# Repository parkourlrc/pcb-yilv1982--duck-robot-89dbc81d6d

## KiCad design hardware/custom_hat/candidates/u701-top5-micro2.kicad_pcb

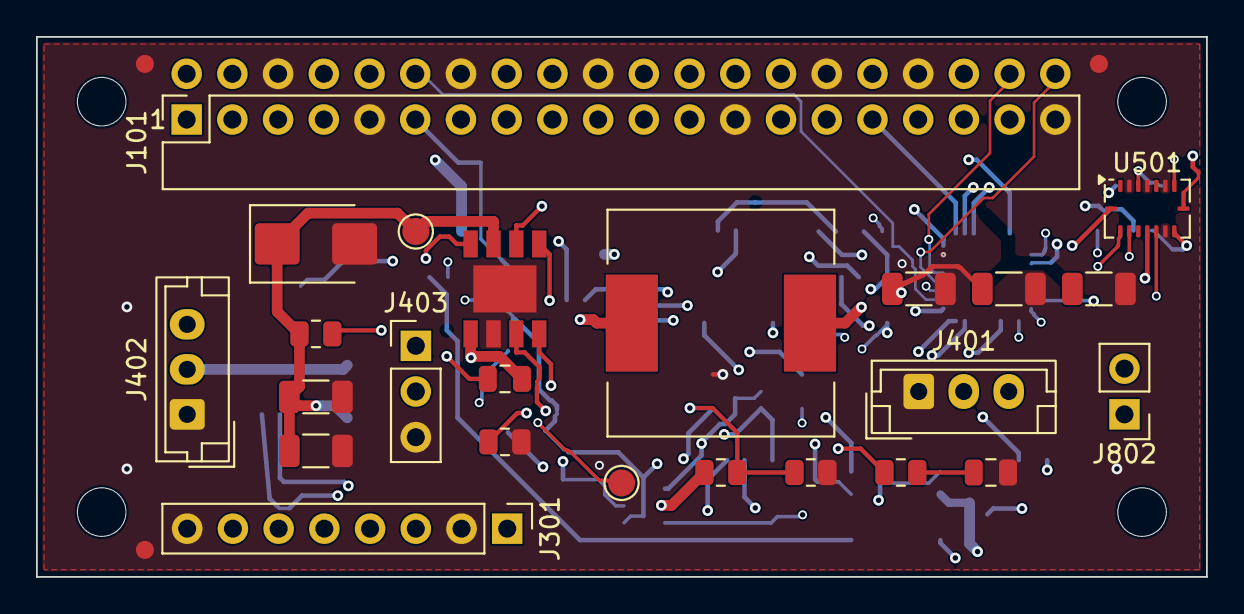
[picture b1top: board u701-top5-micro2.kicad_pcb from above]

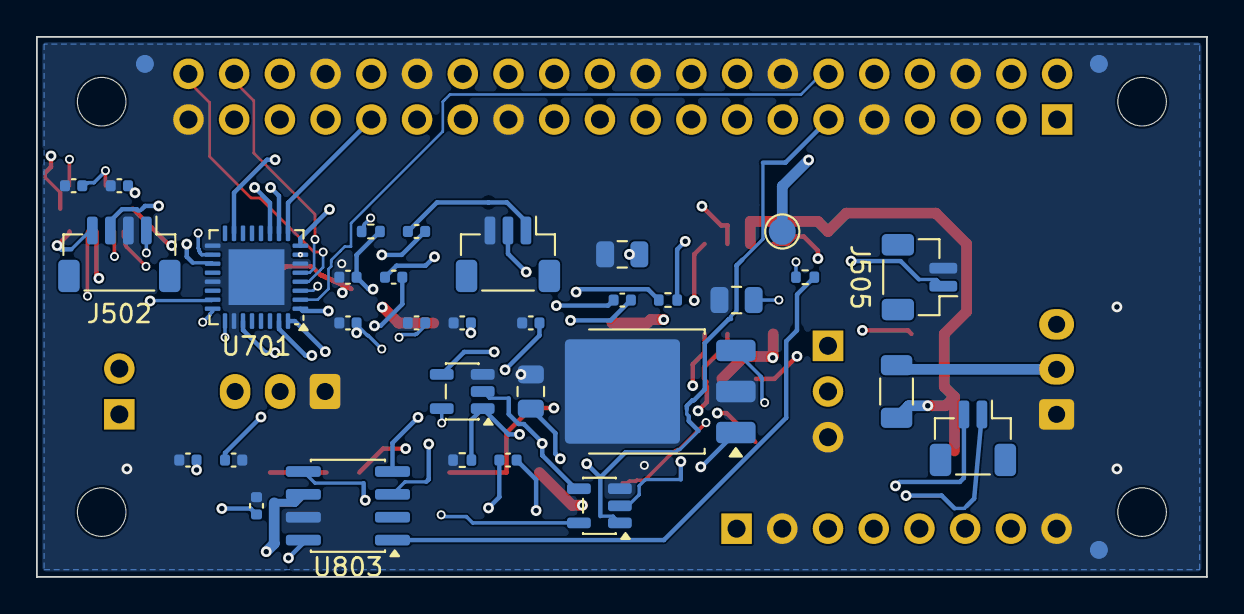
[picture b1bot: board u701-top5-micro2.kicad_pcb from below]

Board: 4 copper layers, 65.0 x 30.0 mm, 66 parts (35 on the bottom side), 41 nets.

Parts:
C301: 3.3nF; C_0805_2012Metric
C302: 100nF; C_0805_2012Metric
C303, C304: 10uF; C_1206_3216Metric
C305, C306: 22uF; C_1206_3216Metric
C307: 22uF reserve; C_1206_3216Metric
C308, C309: 1uF; C_0805_2012Metric
C310, C312, C319, C320, C327: 100nF; C_0402_1005Metric
C311, C313, C315, C321, C322, C325, C326: 1uF; C_0402_1005Metric
C317, C318: 10uF; C_0402_1005Metric
C323: 10uF; C_0805_2012Metric
D301: SMBJ12A (fitted); D_SMB
FID1, FID2, FID3, FID4, FID5, FID6: Fiducial_1mm
H1, H2, H3, H4: MountingHole_2.7mm_M2.5
J101: RADXA_ZERO_3W_40P; PinSocket_2x20_P2.54mm_Vertical
J301: POWER_AND_RAILS; PinHeader_1x08_P2.54mm_Vertical
J401: DYNAMIXEL_TTL_1; JST_EH_B3B-EH-A_1x03_P2.50mm_Vertical
J402: DYNAMIXEL_TTL_2; JST_EH_B3B-EH-A_1x03_P2.50mm_Vertical
J403: HOST_UART2; PinHeader_1x03_P2.54mm_Vertical
J502: TOF_I2C5; JST_SH_BM04B-SRSS-TB_1x04-1MP_P1.00mm_Vertical
J504: AUDIO_OUT_SH; JST_SH_BM03B-SRSS-TB_1x03-1MP_P1.00mm_Vertical
J505: MIC_IN; JST_SH_BM02B-SRSS-TB_1x02-1MP_P1.00mm_Vertical
J506: SPEAKER; JST_SH_BM02B-SRSS-TB_1x02-1MP_P1.00mm_Vertical
J802: IMU_INT_TP; PinHeader_1x02_P2.54mm_Vertical
L301: 5.5uH; L_12x12mm_H8mm
R301: 52.3k; R_0805_2012Metric
R302: 10k; R_0805_2012Metric
R303: 200k; R_0805_2012Metric
R304: 14k; R_0805_2012Metric
R305: 100k; R_0805_2012Metric
R308: 10k; R_0402_1005Metric
R309: 0R; R_1206_3216Metric
R310, R311: 100k; R_0402_1005Metric
R312: 2.2k; R_0402_1005Metric
TP801: VBATT_2S_IN; TestPoint_Pad_D1.5mm
TP802: +5V; TestPoint_Pad_D1.5mm
TP803: +3V3; TestPoint_Pad_D1.5mm
U301: AP64350; SO-8EP_AP64350
U501: BMI088; Bosch_LGA-16_4.5x3mm_P0.5mm_LayoutBorder7x1y_ClockwisePinNu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
U701: TLV320AIC3104; VQFN-32-1EP_5x5mm_P0.5mm_EP3.1x3.1mm
U702: LP38693DT-1.8 codec 1V8; TO-252-3_TabPin2
U801: SN74LVC1G126; SOT-23-5
U802: SN74LVC1G125; SOT-23-5
U803: PAM8302A; SOIC-8_3.9x4.9mm_P1.27mm

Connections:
+1V8_CODEC: C309.1, C311.1, J301.6, U701.32, U702.1
+3V3: C308.1, C312.1, C313.1, C315.1, C319.1, C320.1, J101.1, J101.17, J301.4, J502.1, R308.2, R311.2, TP803.1, U501.3, U501.7, U501.11, U501.14, U501.15, U701.7, U701.18, U701.24, U701.25, U702.3, U801.5, U802.5
+5V: C305.1, C306.1, C307.1, C323.1, J101.2, J101.4, J301.3, L301.2, R301.1, TP802.1, U803.6
+5V_FB: R301.2, R302.1, U301.5
AUDIO_AMP_EN: R311.1, U803.1
AUDIO_AMP_INN: C322.1, U803.4
AUDIO_AMP_INP: C321.2, U803.3
AUDIO_HP_L: C317.1, U701.19
AUDIO_HP_R: C318.1, U701.23
AUDIO_L: C317.2, J504.1
AUDIO_LINE_L: C321.1, U701.27
AUDIO_MIC: C325.1, J505.1, R312.2
AUDIO_MIC_AC: C325.2, U701.10
AUDIO_MIC_BIAS: C327.1, R312.1, U701.15
AUDIO_MIC_REF: C326.2, U701.11
AUDIO_R: C318.2, J504.2
BMI_INT1_TP: J802.1, U501.16
BMI_INT3_TP: J802.2, U501.12
BUCK_BST: C302.1, U301.1
BUCK_COMP: R304.1, U301.6
BUCK_EN: R305.2, U301.3
BUCK_RT: R303.1, U301.4
BUCK_SW: C302.2, L301.1, U301.8
CODEC_RST: C310.1, R308.1, U701.31
COMP_RC: C301.1, R304.2
DXL_DATA: J401.3, J402.3, U801.4, U802.2
DXL_DIR: J101.11, R310.1, U801.1, U802.1
I2C5_SCL: J101.29, J502.3, U501.8, U701.8
I2C5_SDA: J101.31, J502.4, U501.9, U701.9
I2S_BCLK: J101.12, U701.2
I2S_LRCK: J101.35, U701.3
I2S_MCLK: J101.13, U701.1
I2S_SDI: J101.38, U701.5
I2S_SDO: J101.40, U701.4
POWER_GND: C301.2, C303.2, C304.2, C305.2, C306.2, C307.2, C308.2, C309.2, C310.2, C311.2, C312.2, C313.2, C315.2, C319.2, C320.2, C322.2, C323.2, C326.1, C327.2, D301.2, J101.6, J101.9, J101.14, J101.20, J101.25, J101.30, J101.34, J101.39, J301.2, J301.8, J401.1, J402.1, J403.3, J502.2, J504.3, J505.2, R302.2, R303.2, R310.2, U301.7, U301.9, U501.2, U501.4, U501.6, U501.10, U701.6, U701.17, U701.21, U701.26, U701.33, U702.2, U801.3, U802.3, U803.7
SERVO_VBAT: J301.7, J401.2, J402.2, R309.2
SPK_N: J506.2, U803.8
SPK_P: J506.1, U803.5
UART2_RX: J101.10, J403.2, U802.4
UART2_TX: J101.8, J403.1, U801.2
VBATT_2S_IN: C303.1, C304.1, D301.1, J301.1, R305.1, R309.1, TP801.1, U301.2

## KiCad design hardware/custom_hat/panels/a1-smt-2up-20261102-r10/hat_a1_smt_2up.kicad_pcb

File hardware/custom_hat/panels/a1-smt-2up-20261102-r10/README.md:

# 失败候选r10：勿用于制造

> **2026-11-03撤出现行，仅历史。** 此拼板缺第二单元Power类别映射；旧DRC0不代表规则完整。使用[r18](../a1-smt-2up-20261102-r18/README.md)并见[勘误](../../../../docs/references/扩展板邮票孔与电源修复/research.md)，本目录及派生文件不再用于制造。

源96dcce92…，但第二单元J301标签复制保存角270°，与原实际绘制角90°不一致，引入0.1101mm丝印间距。已修复生成器并由[r11](../a1-smt-2up-20261102-r11/README.md)替代。保留原文件与失败DRC供追溯，未外发/下单。

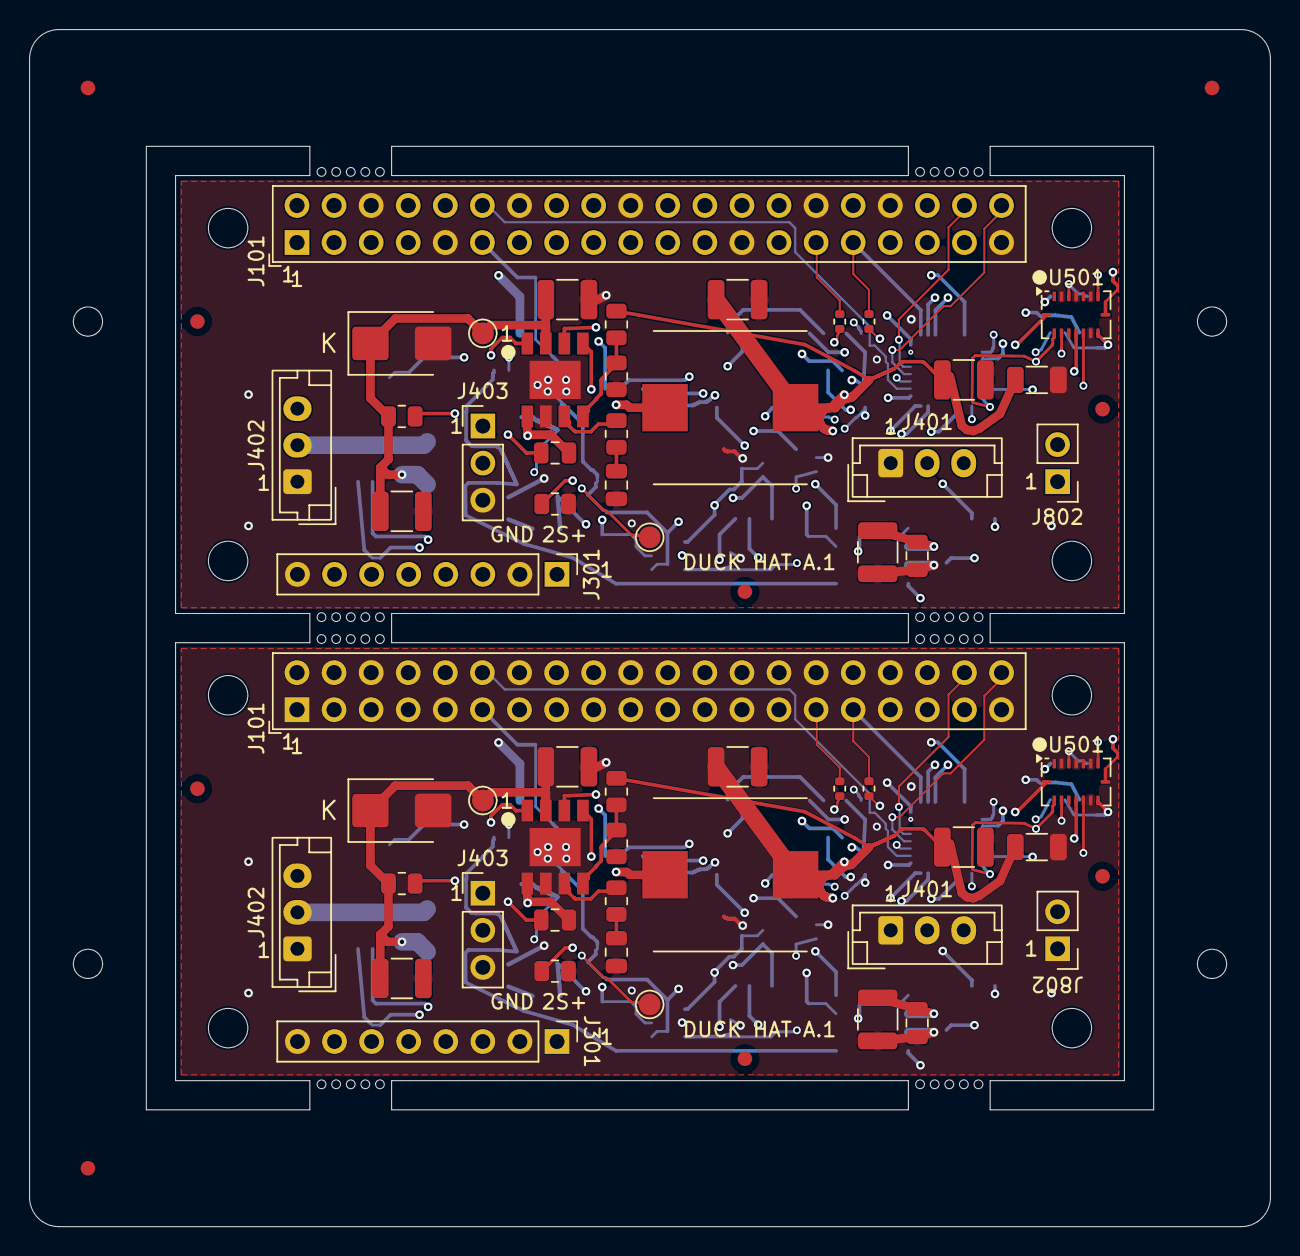
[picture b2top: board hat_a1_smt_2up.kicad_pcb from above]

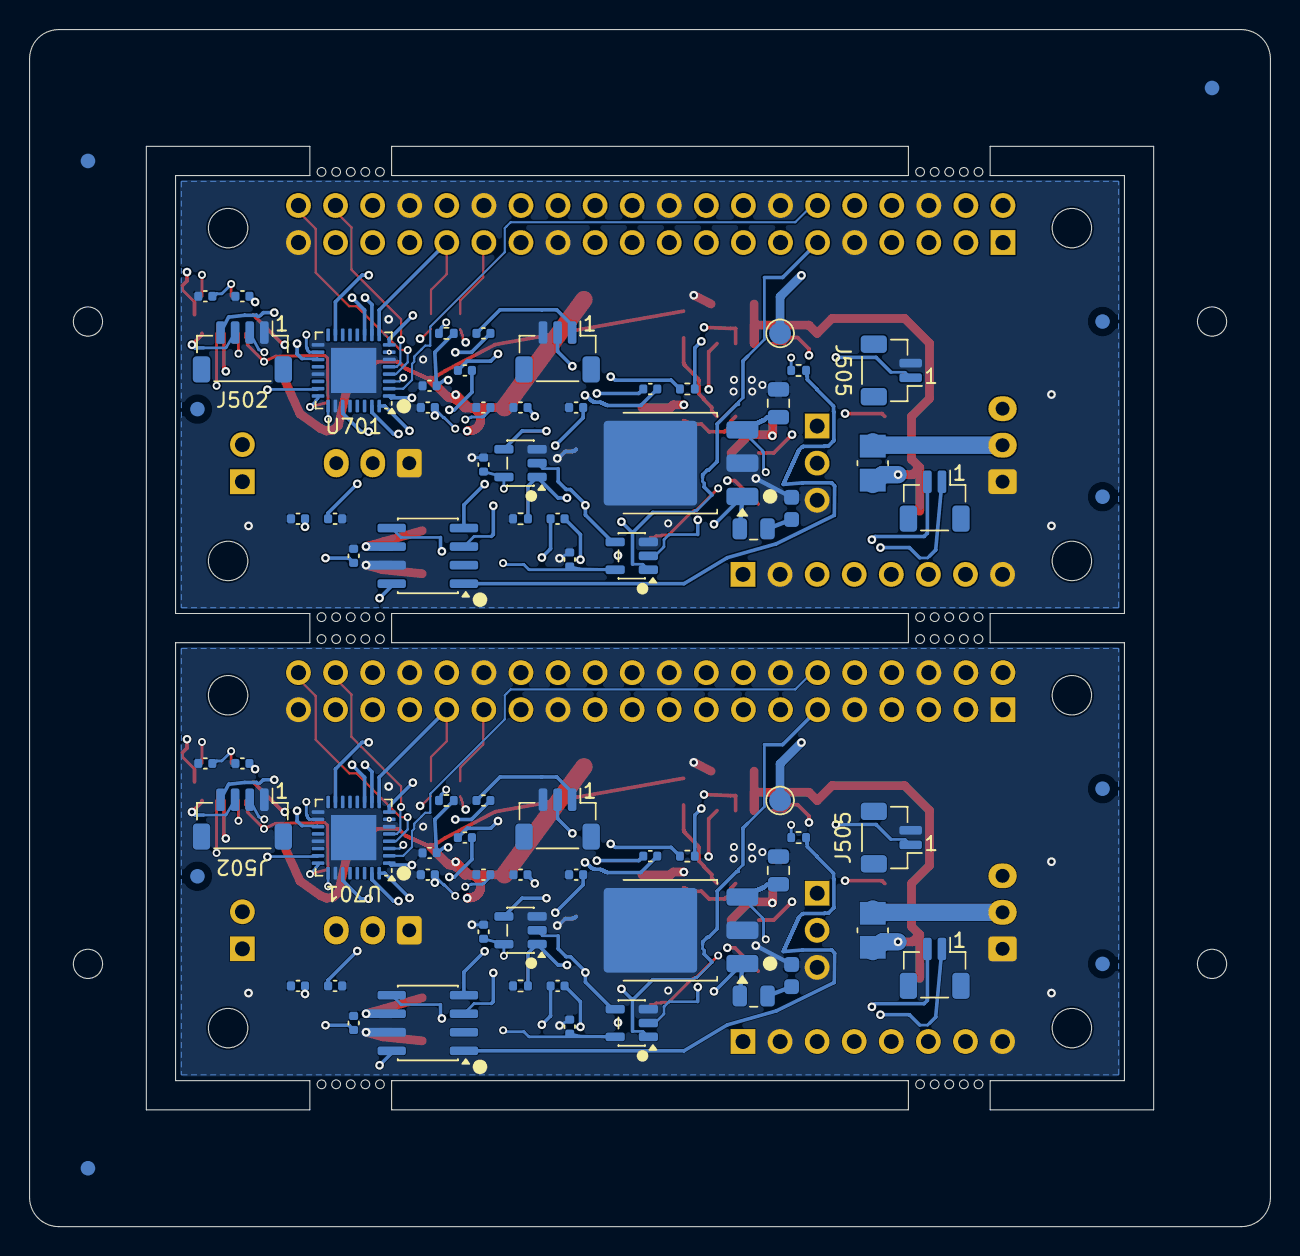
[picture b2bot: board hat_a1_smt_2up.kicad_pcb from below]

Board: 4 copper layers, 85.0 x 82.0 mm, 194 parts (77 on the bottom side), 84 nets.

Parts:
B2_C301: 3.3nF; C_0805_2012Metric
B2_C302: 100nF; C_0805_2012Metric
B2_C303, B2_C304, B2_C305, B2_C306, B2_C323: 22uF; C_1210_3225Metric
B2_C307: 22uF reserve; C_1206_3216Metric
B2_C308, B2_C328: 2.2uF; C_0805_2012Metric
B2_C309: 2.2uF; C_0805_2012Metric_LDO_ClearSilk
B2_C310, B2_C312, B2_C319, B2_C320, B2_C327, B2_C329, B2_C330: 100nF; C_0402_1005Metric
B2_C311, B2_C313, B2_C315, B2_C321, B2_C322, B2_C325, B2_C326: 1uF; C_0402_1005Metric
B2_C317, B2_C318: 10uF; C_0402_1005Metric
B2_D301: SMBJ12A (fitted); D_SMB
B2_FID1, B2_FID2, B2_FID3, B2_FID4, B2_FID5, B2_FID6: Fiducial_1mm_Mask2mm
B2_H1, B2_H2: MountingHole_2.7mm_M2.5; MountingHole_2.7_M2.5_Head4.5
B2_H3, B2_H4: MountingHole_2.7mm_M2.5
B2_J101: RADXA_ZERO_3W_40P; Radxa40P_Samtec_SSW120
B2_J301: POWER_AND_RAILS; Samtec_TSW108_07
B2_J401: DYNAMIXEL_TTL_1; JST_EH_B3B-EH-A_1x03_P2.50mm_Vertical
B2_J402: DYNAMIXEL_TTL_2; JST_EH_B3B-EH-A_1x03_P2.50mm_Vertical
B2_J403: HOST_UART2; Samtec_TSW103_07
B2_J502: TOF_I2C5; JST_SH_BM04B-SRSS-TB_1x04-1MP_P1.00mm_Vertical
B2_J504: AUDIO_OUT_SH; JST_SH_BM03B-SRSS-TB_1x03-1MP_P1.00mm_Vertical
B2_J505: MIC_IN; JST_SH_BM02B-SRSS-TB_1x02-1MP_P1.00mm_Vertical
B2_J506: SPEAKER; JST_SH_BM02B-SRSS-TB_1x02-1MP_P1.00mm_Vertical
B2_J802: IMU_INT_TP; Samtec_TSW102_07
B2_L301: 5.6uH; IHLP4040DZ_5A_Above2u2
B2_R301: 52.3k; R_0805_2012Metric
B2_R302: 10k; R_0805_2012Metric
B2_R303: 200k; R_0805_2012Metric
B2_R304: 14k; R_0805_2012Metric
B2_R305: 100k; R_0805_2012Metric
B2_R308: 10k; R_0402_1005Metric
B2_R309: 0R; Vishay_WSL1206_Jumper
B2_R310, B2_R311: 100k; R_0402_1005Metric
B2_R312: 2.2k; R_0402_1005Metric
B2_R501, B2_R502: 4.7k; R_0402_1005Metric
B2_R703: 0.047; Vishay_WSLP0603_Damping
B2_TP801: VBATT_2S_IN; TestPoint_Pad_D1.5mm
B2_TP802: +5V; TestPoint_Pad_D1.5mm
B2_TP803: +3V3; TestPoint_Pad_D1.5mm
B2_U301: AP64350; SO-8EP_AP64350
B2_U501: BMI088; Bosch_LGA-16_4.5x3mm_P0.5mm_LayoutBorder7x1y_ClockwisePinNu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
B2_U701: TLV320AIC3104; VQFN-32-1EP_5x5mm_P0.5mm_EP3.1x3.1mm
B2_U702: LP38691DT-1.8; TO-252-3_TabPin2
B2_U801: SN74LVC1G126; SOT-23-5
B2_U802: SN74LVC1G125; SOT-23-5
B2_U803: PAM8302A; SOIC-8_3.9x4.9mm_P1.27mm
C301: 3.3nF; C_0805_2012Metric
C302: 100nF; C_0805_2012Metric
C303, C304, C305, C306, C323: 22uF; C_1210_3225Metric
C307: 22uF reserve; C_1206_3216Metric
C308, C328: 2.2uF; C_0805_2012Metric
C309: 2.2uF; C_0805_2012Metric_LDO_ClearSilk
C310, C312, C319, C320, C327, C329, C330: 100nF; C_0402_1005Metric
C311, C313, C315, C321, C322, C325, C326: 1uF; C_0402_1005Metric
C317, C318: 10uF; C_0402_1005Metric
D301: SMBJ12A (fitted); D_SMB
FID1, FID2, FID3, FID4, FID5, FID6: Fiducial_1mm_Mask2mm
H1, H2: MountingHole_2.7mm_M2.5; MountingHole_2.7_M2.5_Head4.5
H3, H4: MountingHole_2.7mm_M2.5
J101: RADXA_ZERO_3W_40P; Radxa40P_Samtec_SSW120
J301: POWER_AND_RAILS; Samtec_TSW108_07
J401: DYNAMIXEL_TTL_1; JST_EH_B3B-EH-A_1x03_P2.50mm_Vertical
J402: DYNAMIXEL_TTL_2; JST_EH_B3B-EH-A_1x03_P2.50mm_Vertical
J403: HOST_UART2; Samtec_TSW103_07
J502: TOF_I2C5; JST_SH_BM04B-SRSS-TB_1x04-1MP_P1.00mm_Vertical
J504: AUDIO_OUT_SH; JST_SH_BM03B-SRSS-TB_1x03-1MP_P1.00mm_Vertical
J505: MIC_IN; JST_SH_BM02B-SRSS-TB_1x02-1MP_P1.00mm_Vertical
J506: SPEAKER; JST_SH_BM02B-SRSS-TB_1x02-1MP_P1.00mm_Vertical
J802: IMU_INT_TP; Samtec_TSW102_07
L301: 5.6uH; IHLP4040DZ_5A_Above2u2
MB1, MB2, MB3, MB4, MB5, MB6, MB7, MB8, MB9, MB10, MB11, MB12, MB13, MB14, MB15, MB16, MB17, MB18, MB19, MB20, MB21, MB22, MB23, MB24, MB25, MB26, MB27, MB28, MB29, MB30, MB31, MB32, MB33, MB34, MB35, MB36, MB37, MB38, MB39, MB40: Panel NPTH
PFID_B1, PFID_B2, PFID_B3: Panel fiducial 1mm/2mm
PFID_F1, PFID_F2, PFID_F3: Panel fiducial 1mm/2mm
PH1, PH2, PH3, PH4: Panel NPTH
R301: 52.3k; R_0805_2012Metric
R302: 10k; R_0805_2012Metric
R303: 200k; R_0805_2012Metric
R304: 14k; R_0805_2012Metric
R305: 100k; R_0805_2012Metric
R308: 10k; R_0402_1005Metric
R309: 0R; Vishay_WSL1206_Jumper
R310, R311: 100k; R_0402_1005Metric
R312: 2.2k; R_0402_1005Metric
R501, R502: 4.7k; R_0402_1005Metric
R703: 0.047; Vishay_WSLP0603_Damping
TP801: VBATT_2S_IN; TestPoint_Pad_D1.5mm
TP802: +5V; TestPoint_Pad_D1.5mm
TP803: +3V3; TestPoint_Pad_D1.5mm
U301: AP64350; SO-8EP_AP64350
U501: BMI088; Bosch_LGA-16_4.5x3mm_P0.5mm_LayoutBorder7x1y_ClockwisePinNu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
U701: TLV320AIC3104; VQFN-32-1EP_5x5mm_P0.5mm_EP3.1x3.1mm
U702: LP38691DT-1.8; TO-252-3_TabPin2
U801: SN74LVC1G126; SOT-23-5
U802: SN74LVC1G125; SOT-23-5
U803: PAM8302A; SOIC-8_3.9x4.9mm_P1.27mm

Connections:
+1V8_CODEC: C309.1, C311.1, J301.6, U701.32, U702.1
+3V3: C308.1, C312.1, C313.1, C315.1, C319.1, C320.1, C329.1, C330.1, J101.1, J101.17, J301.4, J502.2, R308.2, R311.2, R501.1, R502.1, TP803.1, U501.3, U501.7, U501.11, U501.14, U501.15, U701.7, U701.18, U701.24, U701.25, U702.3, U801.5, U802.5
+5V: C305.1, C306.1, C307.1, C323.1, C328.1, J101.2, J101.4, J301.3, L301.2, R301.1, TP802.1, U803.6
+5V_FB: R301.2, R302.1, U301.5
AUDIO_AMP_EN: R311.1, U803.1
AUDIO_AMP_INN: C322.1, U803.4
AUDIO_AMP_INP: C321.2, U803.3
AUDIO_HP_L: C317.1, U701.19
AUDIO_HP_R: C318.1, U701.23
AUDIO_L: C317.2, J504.1
AUDIO_LINE_L: C321.1, U701.27
AUDIO_MIC: C325.1, J505.1, R312.2
AUDIO_MIC_AC: C325.2, U701.10
AUDIO_MIC_BIAS: C327.1, R312.1, U701.15
AUDIO_MIC_REF: C326.2, U701.11
AUDIO_R: C318.2, J504.2
B2/+1V8_CODEC: B2_C309.1, B2_C311.1, B2_J301.6, B2_U701.32, B2_U702.1
B2/+3V3: B2_C308.1, B2_C312.1, B2_C313.1, B2_C315.1, B2_C319.1, B2_C320.1, B2_C329.1, B2_C330.1, B2_J101.1, B2_J101.17, B2_J301.4, B2_J502.2, B2_R308.2, B2_R311.2, B2_R501.1, B2_R502.1, B2_TP803.1, B2_U501.3, B2_U501.7, B2_U501.11, B2_U501.14, B2_U501.15, B2_U701.7, B2_U701.18, B2_U701.24, B2_U701.25, B2_U702.3, B2_U801.5, B2_U802.5
B2/+5V: B2_C305.1, B2_C306.1, B2_C307.1, B2_C323.1, B2_C328.1, B2_J101.2, B2_J101.4, B2_J301.3, B2_L301.2, B2_R301.1, B2_TP802.1, B2_U803.6
B2/+5V_FB: B2_R301.2, B2_R302.1, B2_U301.5
B2/AUDIO_AMP_EN: B2_R311.1, B2_U803.1
B2/AUDIO_AMP_INN: B2_C322.1, B2_U803.4
B2/AUDIO_AMP_INP: B2_C321.2, B2_U803.3
B2/AUDIO_HP_L: B2_C317.1, B2_U701.19
B2/AUDIO_HP_R: B2_C318.1, B2_U701.23
B2/AUDIO_L: B2_C317.2, B2_J504.1
B2/AUDIO_LINE_L: B2_C321.1, B2_U701.27
B2/AUDIO_MIC: B2_C325.1, B2_J505.1, B2_R312.2
B2/AUDIO_MIC_AC: B2_C325.2, B2_U701.10
B2/AUDIO_MIC_BIAS: B2_C327.1, B2_R312.1, B2_U701.15
B2/AUDIO_MIC_REF: B2_C326.2, B2_U701.11
B2/AUDIO_R: B2_C318.2, B2_J504.2
B2/BMI_INT1_TP: B2_J802.1, B2_U501.16
B2/BMI_INT3_TP: B2_J802.2, B2_U501.12
B2/BUCK_BST: B2_C302.1, B2_U301.1
B2/BUCK_COMP: B2_R304.1, B2_U301.6
B2/BUCK_EN: B2_R305.2, B2_U301.3
B2/BUCK_RT: B2_R303.1, B2_U301.4
B2/BUCK_SW: B2_C302.2, B2_L301.1, B2_U301.8
B2/CODEC_RST: B2_C310.1, B2_J101.33, B2_R308.1, B2_U701.31
B2/COMP_RC: B2_C301.1, B2_R304.2
B2/DXL_DATA: B2_J401.3, B2_J402.3, B2_U801.4, B2_U802.2
B2/DXL_DIR: B2_J101.11, B2_R310.1, B2_U801.1, B2_U802.1
B2/I2C5_SCL: B2_J101.29, B2_J502.4, B2_R501.2, B2_U501.8, B2_U701.8
B2/I2C5_SDA: B2_J101.31, B2_J502.3, B2_R502.2, B2_U501.9, B2_U701.9
B2/I2S_BCLK: B2_J101.12, B2_U701.2
B2/I2S_LRCK: B2_J101.35, B2_U701.3
B2/I2S_MCLK: B2_J101.13, B2_U701.1
B2/I2S_SDI: B2_J101.38, B2_U701.5
B2/I2S_SDO: B2_J101.40, B2_U701.4
B2/LDO_CAP_RETURN: B2_C309.2, B2_R703.1
B2/POWER_GND: B2_C301.2, B2_C303.2, B2_C304.2, B2_C305.2, B2_C306.2, B2_C307.2, B2_C308.2, B2_C310.2, B2_C311.2, B2_C312.2, B2_C313.2, B2_C315.2, B2_C319.2, B2_C320.2, B2_C322.2, B2_C323.2, B2_C326.1, B2_C327.2, B2_C328.2, B2_C329.2, B2_C330.2, B2_D301.2, B2_J101.6, B2_J101.9, B2_J101.14, B2_J101.20, B2_J101.25, B2_J101.30, B2_J101.34, B2_J101.39, B2_J301.2, B2_J301.8, B2_J401.1, B2_J402.1, B2_J403.3, B2_J502.1, B2_J504.3, B2_J505.2, B2_R302.2, B2_R303.2, B2_R310.2, B2_R703.2, B2_U301.7, B2_U301.9, B2_U501.2, B2_U501.4, B2_U501.6, B2_U501.10, B2_U701.6, B2_U701.17, B2_U701.21, B2_U701.26, B2_U701.33, B2_U702.2, B2_U801.3, B2_U802.3, B2_U803.7
B2/SERVO_VBAT: B2_J301.7, B2_J401.2, B2_J402.2, B2_R309.2
B2/SPK_N: B2_J506.2, B2_U803.8
B2/SPK_P: B2_J506.1, B2_U803.5
B2/UART2_RX: B2_J101.10, B2_J403.2, B2_U802.4
B2/UART2_TX: B2_J101.8, B2_J403.1, B2_U801.2
B2/VBATT_2S_IN: B2_C303.1, B2_C304.1, B2_D301.1, B2_J301.1, B2_R305.1, B2_R309.1, B2_TP801.1, B2_U301.2
BMI_INT1_TP: J802.1, U501.16
BMI_INT3_TP: J802.2, U501.12
BUCK_BST: C302.1, U301.1
BUCK_COMP: R304.1, U301.6
BUCK_EN: R305.2, U301.3
BUCK_RT: R303.1, U301.4
BUCK_SW: C302.2, L301.1, U301.8
CODEC_RST: C310.1, J101.33, R308.1, U701.31
COMP_RC: C301.1, R304.2
DXL_DATA: J401.3, J402.3, U801.4, U802.2
DXL_DIR: J101.11, R310.1, U801.1, U802.1
I2C5_SCL: J101.29, J502.4, R501.2, U501.8, U701.8
I2C5_SDA: J101.31, J502.3, R502.2, U501.9, U701.9
I2S_BCLK: J101.12, U701.2
I2S_LRCK: J101.35, U701.3
I2S_MCLK: J101.13, U701.1
I2S_SDI: J101.38, U701.5
I2S_SDO: J101.40, U701.4
LDO_CAP_RETURN: C309.2, R703.1
POWER_GND: C301.2, C303.2, C304.2, C305.2, C306.2, C307.2, C308.2, C310.2, C311.2, C312.2, C313.2, C315.2, C319.2, C320.2, C322.2, C323.2, C326.1, C327.2, C328.2, C329.2, C330.2, D301.2, J101.6, J101.9, J101.14, J101.20, J101.25, J101.30, J101.34, J101.39, J301.2, J301.8, J401.1, J402.1, J403.3, J502.1, J504.3, J505.2, R302.2, R303.2, R310.2, R703.2, U301.7, U301.9, U501.2, U501.4, U501.6, U501.10, U701.6, U701.17, U701.21, U701.26, U701.33, U702.2, U801.3, U802.3, U803.7
SERVO_VBAT: J301.7, J401.2, J402.2, R309.2
SPK_N: J506.2, U803.8
SPK_P: J506.1, U803.5
UART2_RX: J101.10, J403.2, U802.4
UART2_TX: J101.8, J403.1, U801.2
VBATT_2S_IN: C303.1, C304.1, D301.1, J301.1, R305.1, R309.1, TP801.1, U301.2
